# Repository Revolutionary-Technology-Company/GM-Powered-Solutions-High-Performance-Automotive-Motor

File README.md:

# GM-Powered-Solutions-High-Performance-Automotive-Motor
This high-performance EV powertrain blueprint retrofits a GM SS 6-speed manual platform with a next-generation electric architecture engineered to outperform Tesla's top-tier drives.

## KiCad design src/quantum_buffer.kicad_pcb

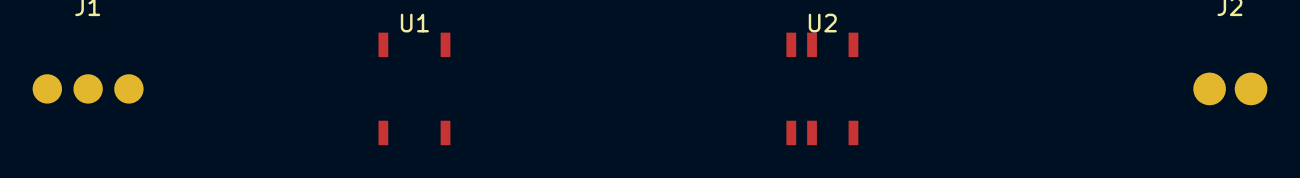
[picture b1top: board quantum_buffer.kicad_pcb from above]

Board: 0 copper layers, 4 parts (0 on the bottom side), 6 nets, no tracks yet.

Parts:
J1: Amphenol_Circular_3Pin_IP69K
J2: TerminalBlock_Phoenix_MPT_0.5-2-2.54
U1: Fractured_Gold_Lattice_SOIC8
U2: SOIC-8_3.9x4.9mm_Pitch1.27mm

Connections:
GND_HIGH_POWER: J2.2, U2.5
GND_ISO: J1.3, U1.4, U2.4
Inverter_Gate_Drive_Signal: J2.1, U2.7
Lattice_Latch_Out: U1.6, U2.2
Pedal_Analog_In: J1.2, U1.2
VCC_5V: J1.1, U1.8, U2.1
